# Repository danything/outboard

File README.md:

# outboard

An external board that powers a PCIe x1 TV tuner card from USB-C and connects it to a PC over the card's internal USB cable.
Status: pre-prototype. Nothing here has been built or tested on real hardware.
License: CERN-OHL-S-2.0.

## 何をする基板か

PLEX PX-MLT8PE のような PCIe x1 のチューナーカードは、PCIe からは電源 (3.3V と 12V) だけを取り、信号はカードの内部 USB ケーブルで出す。
outboard はその電源を USB-C (PD 9V) から作り、内部 USB を USB-C で PC へつなぐ。カードを PC の外に置ける。

- USB-C 2 口: J1 = PC へのデータ + 給電、J2 = 給電だけ
- カードの内部 USB の口 2 つ (機器 2 台) を、基板のハブ (CH334P) でまとめて J1 へ。カードとは JST PH 4 ピンのケーブル 2 本
- PCIe x1 のスロット J3 は基板の端をはさむ形 (straddle)。カードは基板と同じ平面に並ぶ (ケースを薄くするため)
- 回路と理由は [docs/design.md](docs/design.md)

## 状態

**rev D・試作前。実機では未検証。** 版の名前は rev D のままだが、KiCad の rev D からハブと PH のコネクタの分 (と外部のレビューでの直し) だけ違う。次の版は rev E。KiCad + Python のスクリプトから [tscircuit](https://tscircuit.com) (TypeScript) へ作り直した (段階 5 の製造用の出力と文書の仕上げが残り)。

| 段階 | 中身                                                                   | 状態                                            |
| ---- | ---------------------------------------------------------------------- | ----------------------------------------------- |
| 0    | リポジトリの土台と CI/CD                                               | 済み                                            |
| 1    | フットプリント (データシートとの突き合わせ)                            | 済み ([docs/footprints.md](docs/footprints.md)) |
| 2    | 回路 (rev D のネットリスト + 変更の表と同じつながり方になることを検査) | 済み (食い違い 0)                               |
| 3    | 基板の検査 (自前)                                                      | 済み ([docs/checks.md](docs/checks.md))         |
| 4    | 配置と配線                                                             | 済み ([docs/routing.md](docs/routing.md))       |
| 5    | 製造用の出力と文書の仕上げ                                             |                                                 |

**回路は入った**: 部品 121 個・ネット 64 本・未接続のパッド 48 個が、rev D (KiCad) のネットリストに意図した変更の表 (`tools/netlist.ts`) を当てたものと完全に同じつながり方になっている (CI が毎回比べる)。
**USB のハブを足した**: カードは内部 USB の口を 2 つ持つ (機器 2 台) ので、2×5 のヘッダ J4 をやめ、ハブ U8 (CH334P) で 2 つに分けて、カードの口と同じ系統の JST PH 4 ピンの表面実装のコネクタ J4・J6 へ出す (両端 PH のケーブル 25cm × 2 本、同じ向き 1 → 1 でつなぐ)。カードの VBUS は専用の U9 (VBUS1 から) と、短絡の保護の PTC F2 を通して出す。基板は 100 × 42mm のまま。**J4・J6 のピンの割り当て (1 VBUS・2 D−・3 D+・4 GND) は元のケーブルの線の色からの推定で、確かめ待ち** (`lib/card-usb.ts` の 1 か所で変えられる。[design.md](docs/design.md#内部-usb-のコネクタ))。
**配線は完了。発注前の最終レビュー待ち。** 部品は `lib/placement.ts` に置き (ブロックごとの配置と、ブロックをまたぐネットの受け渡しの点。配置だけの絵は [`placement.circuit-pcb.snap.svg`](__snapshots__/placement.circuit-pcb.snap.svg))、銅は `lib/routing/` にブロックごとの別ファイルで書いてある ([docs/routing.md](docs/routing.md))。基板は 100 × 42mm ([docs/mechanical.md](docs/mechanical.md#寸法))・2 層。部品番号はうらのシルク (`lib/refdes.tsx`)。
**検査は全部 0** (CI とリリースが毎回): 自前の検査は `bun checks/run.ts --strict` で指摘 0・飛ばし 0、回路の値 0、rev D とのネットリストの食い違い 0、KiCad の DRC は `lib_footprint_issues` (書き出しの名前の都合) のほか 0。ブロックをつなぐ所は検査 `handoffs`、うらの GND は `groundPlane` が見る。
D1・D2 の放熱は、このまま試作して温度を測る (持ち主の判断)。5V の入力のときは、ファームウェアが最初から 3.3V の負荷を制限する。rev E の候補: 理想ダイオード (TPS2121 など) への置き換え、カードの VBUS の U9 を過熱の保護つきの LDO に (どちらも試作の結果しだい)。製造で確かめることと、余裕の小さい所は [docs/manufacturing.md](docs/manufacturing.md#見積もりの画面で見る所)。

KiCad の版は main から消した。タグ [`kicad-rev-c`](../../tree/kicad-rev-c) (rev C。検査 0) と
ブランチ [`rev-d`](../../tree/rev-d) (rev D の途中。回路図とライブラリまで) に残っている。

## 主な仕様

| 項目     | 値                                                                                                                      |
| -------- | ----------------------------------------------------------------------------------------------------------------------- |
| 入力     | USB-C ×2、USB PD 9V (CH224A ×2)。2 口を SS54 で合流                                                                     |
| 出力     | 3.3V・3A (TPS62933)、12V・0.5A (MT3608B)。12V は AO3401A + PTC で入り切り、過電圧で遮断                                 |
| マイコン | CH32V003 (電源の順序・監視・LED)                                                                                        |
| 基板     | 2 層・厚み 1.6mm (J3 のため)。100 × 42mm                                                                                |
| ケース   | 光造形 (JLC3DP の 9600)。外形 約 145 × 151 × 21mm (カードの寸法は推定。[docs/mechanical.md](docs/mechanical.md#ケース)) |

## 見方

- ブラウザで見る (main の最新。基板・回路図・3D): <https://danything.github.io/outboard/>
- 絵は [`__snapshots__/`](__snapshots__/) にある (回路図・おもてとうら・おもて・うら・3D)。PR では絵の差分として変化が見える
- 3D の絵は部品を載せた姿 (形は [`lib/cad.ts`](lib/cad.ts) がデータシートの寸法から作る簡単なもの)。カードとブラケットは推定の寸法で、半透明・途中で切って描く (発注のデータには入らない)。
  斜め上・真上・横・USB-C の側の 4 枚 (`tools/render3d.ts`)。Pages にも同じ絵がある (`index/3d.png`・`index/3d-top.png`・`index/3d-side.png`・`index/3d-usb.png`)

| 回路図                                                    | 3D                                             |
| --------------------------------------------------------- | ---------------------------------------------- |
|  |  |

| 3D (USB-C とブラケットの側)                              | 3D (真上)                                               |
| -------------------------------------------------------- | ------------------------------------------------------- |
|  |  |

## 作り方

道具はコンテナだけ (ホストに Bun も Node も入れない)。CI と同じイメージの中で動かす。中身は [compose.yml](compose.yml)。

```sh
docker compose up dev               # 起動。http://localhost:3020 に基板・回路図・3D (保存すると描き直す)
docker compose run --rm check       # 検査。CI の build と同じ一式 (下の script を全部)
docker compose run --rm snapshots   # 絵の更新 (__snapshots__ を描き直す)
docker compose run --rm kicad-drc   # KiCad の DRC。check に続けて KiCad の DRC と判定 (CI の全部)
```

- Zed で書くとき: コードは Zed、動く画面は横のブラウザで <http://localhost:3020> (main の最新でよければ [Pages](https://danything.github.io/outboard/))。
  絵だけ見るなら `__snapshots__/`。変えたら `snapshots` で描き直して、差分ごとコミットする
- wslc には compose が無い (3.0)。同じ中身を `run` で動かす。起動は下の 1 行。ほかは `-p` と `-e` を外し、`sh -c` の中身を compose.yml の `command` に替える
  (KiCad の DRC は `check` のあと、`--user 0 -w /work/dist/index/kicad kicad/kicad:10.0` で `kicad-cli`、続けて Bun で判定)。Git Bash では前に `MSYS_NO_PATHCONV=1` を付ける

```sh
wslc run --rm -it -p 127.0.0.1:3020:3020 -e CHOKIDAR_USEPOLLING=true -v .:/work -v outboard_node_modules:/work/node_modules -w /work oven/bun:1.4.4 sh -c "bun install --frozen-lockfile && bunx tsci dev"
```

script を 1 つずつ動かすときは、中に入る (`docker compose run --rm check bash`)。

```sh
bun run build      # dist/ に circuit.json・絵・KiCad の基板・見るためのページ
bun run check      # 型検査 (bun check)・テスト (bun test)・自前の検査 (基板・回路の値・rev D とのネットリストの比べ)
bun run snapshot   # __snapshots__ の絵と同じか。変えたときは bun run snapshot --update
bun run fab        # dist/fab/ に製造用のファイル一式
bun run case       # dist/case/ にケース (皿・ふた・ハッチ) の STL と STEP、絵 (先に build)
bun run lint       # oxlint と bun fmt --check。直すときは bun run format
```

- 版は全部固定してある (tscircuit は 0.0.x が 1 日に何度も出る)。上げるのは Renovate
- ビルドは外の部品検索に問い合わせない (`--disable-parts-engine`)。設計を tscircuit.com に送らない
- `tsci dev` には切る指定が無く、部品の品番を外の部品検索に問い合わせることがある (tscircuit 0.0.3161 の `<board>` にも切る指定は無い)
- `typescript` は入れていない。型検査は `bun check`。`circuit-json` は circuit.json の型のために入れてある

| 場所                          | 中身                                                                                                                                                                                                                              |
| ----------------------------- | --------------------------------------------------------------------------------------------------------------------------------------------------------------------------------------------------------------------------------- |
| `index.circuit.tsx`           | 基板の全体                                                                                                                                                                                                                        |
| `lib/`                        | `blocks.tsx` (ブロックごとの回路)・`parts.tsx` (部品。ピンとネットを型で縛る)・`nets.ts` (ネットの一覧)・`footprints.ts` (ランド)・`placement.ts` (位置)・`routing/` (銅。ブロックごと)・`geometry.ts` (外形)・`revision.ts` (版) |
| `land-patterns.circuit.tsx`   | 全部のランドを並べた見本 (作る基板ではない)                                                                                                                                                                                       |
| `checks/`                     | circuit.json を読む自前の検査と、検査のテスト。`board.ts` (基板)・`design.ts` (分圧の値・定格など、回路の意図)                                                                                                                    |
| `case/`                       | ケース (replicad)。`card.ts` (カードの推定の寸法)・`layout.ts` (形)・`case.test.ts` (中身と重ならないか)                                                                                                                          |
| `tools/`                      | 製造用の出力・スナップショット・KiCad の DRC の判定・`netlist.ts` (rev D とのネットリストの比べ)                                                                                                                                  |
| `fixtures/rev-d-netlist.json` | rev D の KiCad のネットリスト (部品と、パッドごとのつながり)。比べる相手                                                                                                                                                          |

## CI/CD

| いつ                                                                | 何をする                                                                                                                                                               |
| ------------------------------------------------------------------- | ---------------------------------------------------------------------------------------------------------------------------------------------------------------------- |
| PR・main への push ([check.yml](.github/workflows/check.yml))       | lint → ビルド (tscircuit の検査を含む) → 型検査・テスト・自前の検査 (rev D とのネットリストの比べを含む) → スナップショット → 製造用の出力 → ケース → **KiCad の DRC** |
| main への push                                                      | 上に加えて、見るためのページを GitHub Pages に出す                                                                                                                     |
| タグ `rev-*` の push ([release.yml](.github/workflows/release.yml)) | 同じ手順で作った製造用のファイルを GitHub Release に添付                                                                                                               |

- **二重の検査**: tscircuit が書き出した KiCad の基板に、KiCad 10 の DRC (`--refill-zones`) をかける。
  つながっていない所・短絡・面を塗り直したあとの間隔を見る。自前の検査との役割の分け方は [docs/checks.md](docs/checks.md)。
  書き出しのせいで出る指摘は、理由を付けて [tools/kicad-drc.ts](tools/kicad-drc.ts) で除外する。決まり ([tools/outboard.kicad_dru](tools/outboard.kicad_dru)) の数字は `checks/rules.ts` と同じ
- **成果物** (Actions の Artifacts): `fab` (ガーバーの zip・BOM・配置表・回路図の PDF・絵・circuit.json・SHA256SUMS)、`case` (ケースの STL・STEP・絵)、`site` (ページ)、`kicad-drc` (DRC の報告)
- **必須のチェック** (ルールセット `default`): `build / build`・`build / kicad-drc`・`claude-review`。緑になるまで main にマージできない。CI のジョブを足したり名前を変えたりしたら、ルールセットも直す: `gh api repos/danything/outboard/rulesets --jq '.[]|select(.name=="default").id'` で id を引き、`gh api -X PUT repos/danything/outboard/rulesets/<id> --input <直した JSON>`
- **スナップショット**: 絵が 1 つでも変わると CI が落ちる。Renovate の PR は、絵が変わらないときだけ自分でマージされる
- **リリース**: `lib/revision.ts` の版 (基板のシルクと同じ) と同じ名前のタグを main のコミットに打って push する。
  **発注するデータは必ずリリースから取る**。同じ版は出し直せないので、基板を変えたら版を上げる

## 文書

| ファイル                                       | 中身                                                               |
| ---------------------------------------------- | ------------------------------------------------------------------ |
| [docs/design.md](docs/design.md)               | ブロック図、ブロックごとの回路、つなぎ方ごとの動き、電力の見積もり |
| [docs/parts.md](docs/parts.md)                 | 部品と選んだ理由、LCSC の品番                                      |
| [docs/footprints.md](docs/footprints.md)       | ランドとデータシートの突き合わせの表、部品データの出どころ         |
| [docs/mechanical.md](docs/mechanical.md)       | 形の選び方、寸法、ブラケット、ケース、実物で測る所                 |
| [docs/firmware.md](docs/firmware.md)           | ファームウェアの仕様、LED の点滅                                   |
| [docs/manufacturing.md](docs/manufacturing.md) | JLCPCB への出し方、見積もり、ケースの JLC3DP への出し方            |
| [docs/bringup.md](docs/bringup.md)             | 試作で最初に測ること、試験の一覧                                   |
| [docs/history.md](docs/history.md)             | rev A〜C のレビューで決めたこと (いまの設計の理由)                 |
| [docs/checks.md](docs/checks.md)               | 基板の検査の一覧、自前の検査と KiCad の DRC の役割の分け方         |
| [docs/routing.md](docs/routing.md)             | 配線の書き方 (ファイルの分け方、層、座標、部品、確かめ方)          |

## ライセンス

[CERN-OHL-S-2.0](LICENSE)

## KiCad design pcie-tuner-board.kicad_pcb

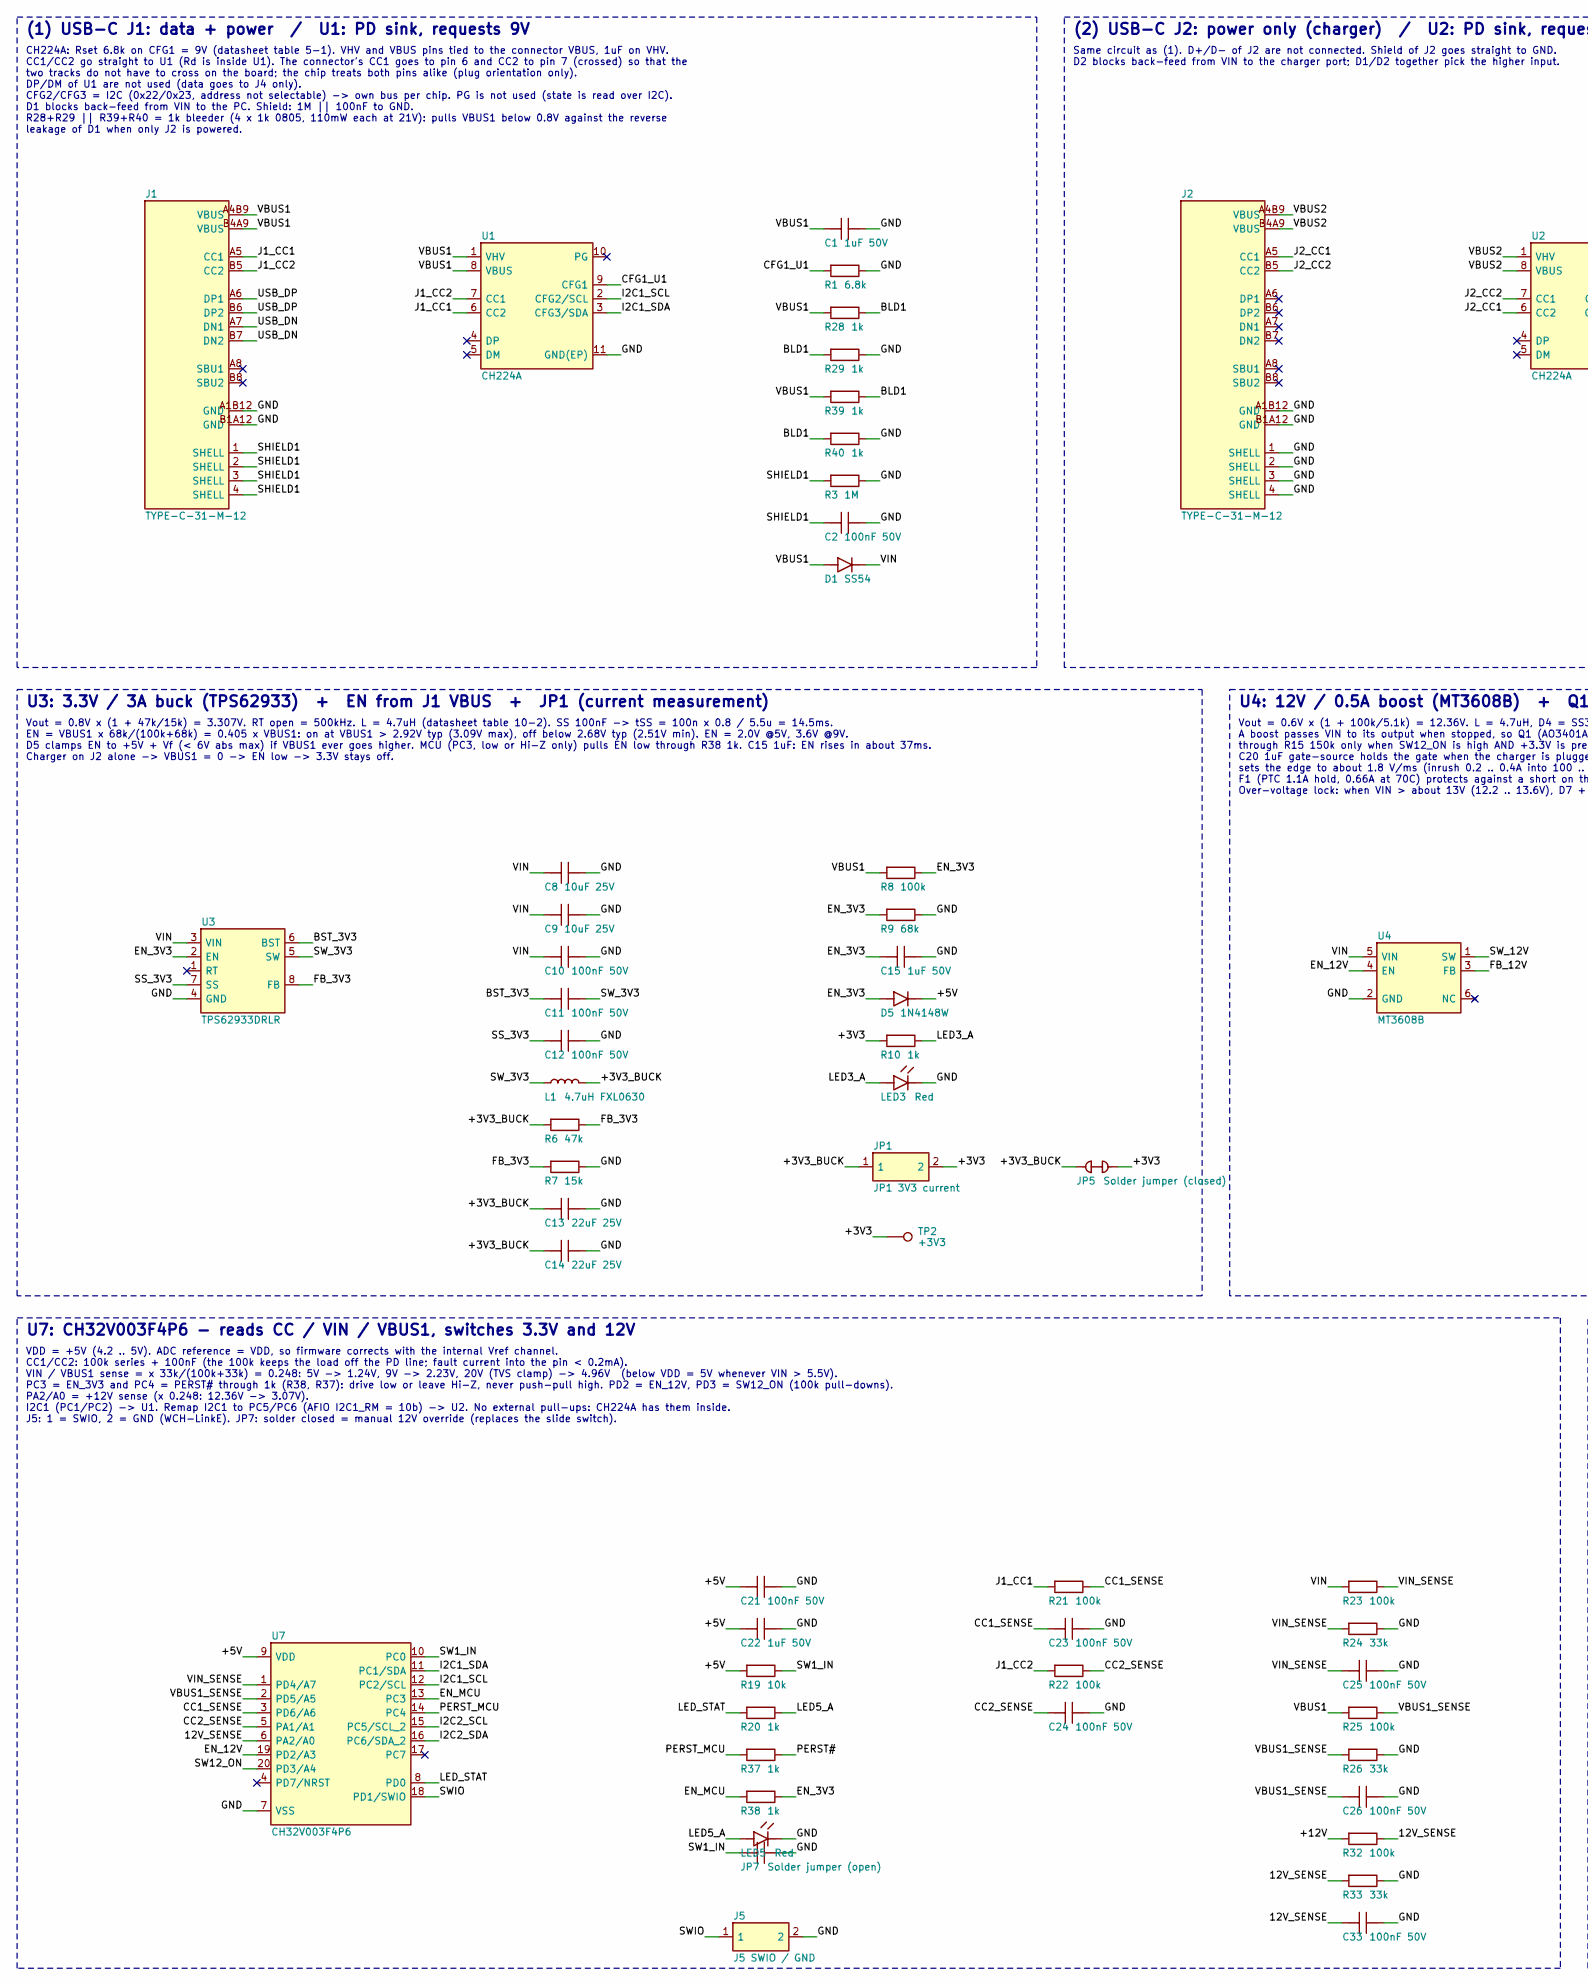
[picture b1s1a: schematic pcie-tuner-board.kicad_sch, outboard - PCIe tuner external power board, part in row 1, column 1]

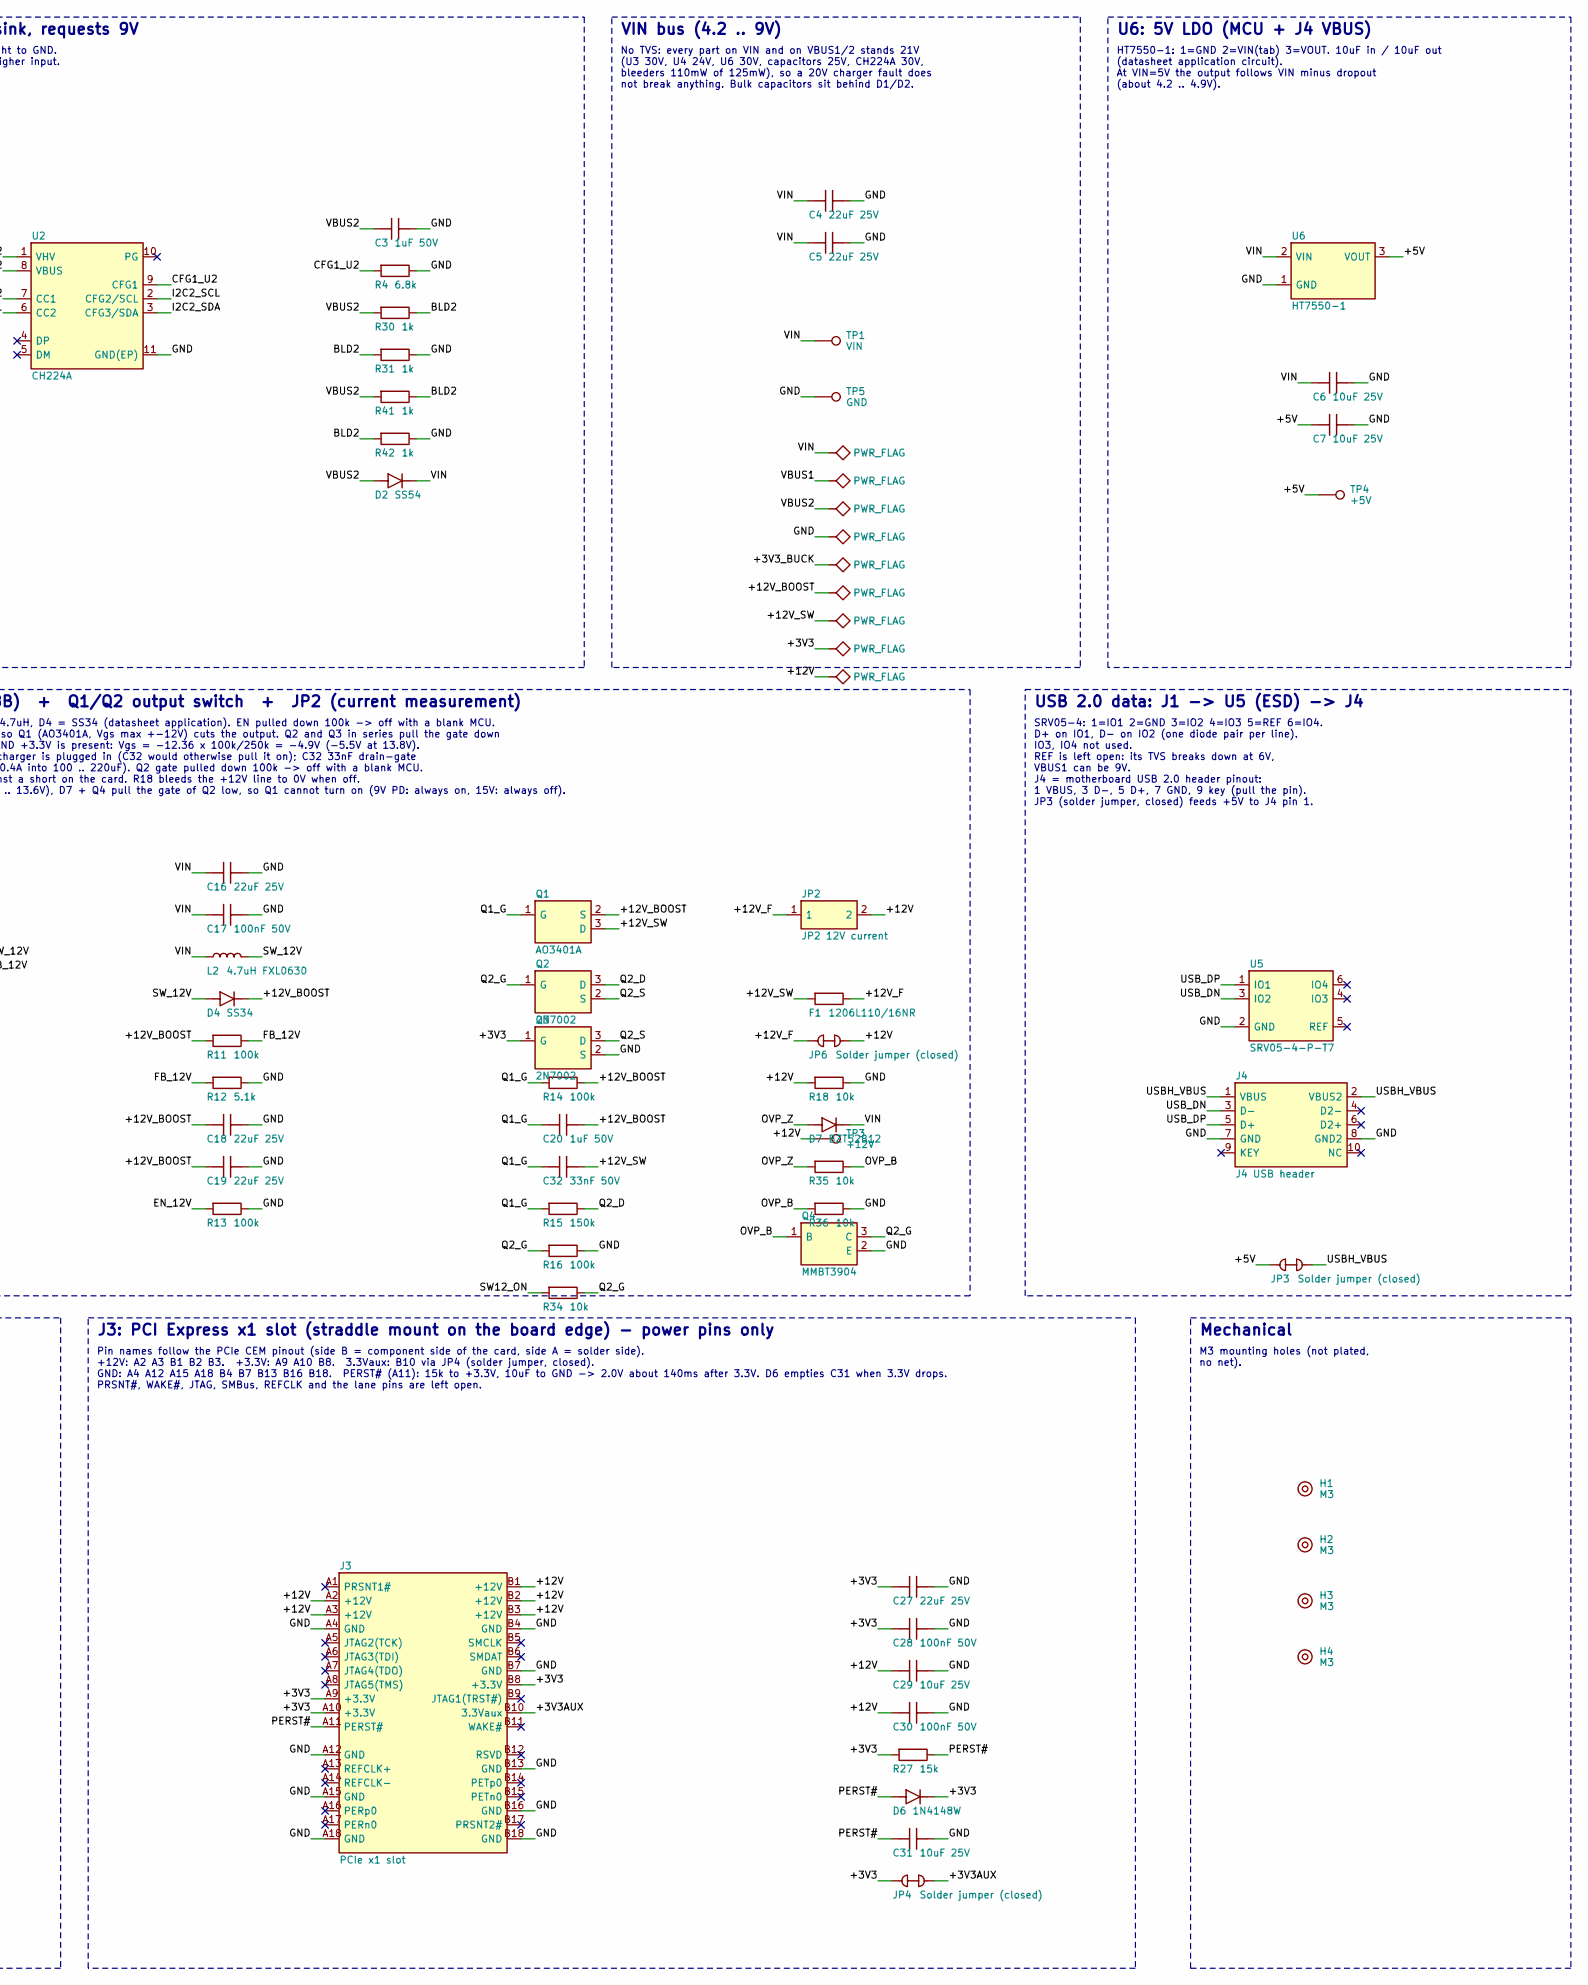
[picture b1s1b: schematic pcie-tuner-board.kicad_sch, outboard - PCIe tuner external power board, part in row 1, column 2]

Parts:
C1, C3, C15, C20, C22: 1uF 50V; C0603; MPN CL10A105KB8NNNC; LCSC C15849
C2, C10, C11, C12, C17, C21, C23, C24, C25, C26, C28, C30, C33: 100nF 50V; C0603; MPN CC0603KRX7R9BB104; LCSC C14663
C4, C5, C13, C14, C16, C18, C19, C27: 22uF 25V; C0805; MPN CL21A226MAQNNNE; LCSC C45783
C6, C7, C8, C9, C29, C31: 10uF 25V; C0805; MPN CL21A106KAYNNNE; LCSC C15850
C32: 33nF 50V; C0603; MPN CL10B333KB8NNNC; LCSC C21117
D1, D2: SS54; SMA_L4.4-W2.8-LS5.4-R-RD; MPN SS54; LCSC C22452
D4: SS34; SMA_L4.3-W2.6-LS5.2-RD; MPN SS34; LCSC C8678
D5, D6: 1N4148W; SOD-123F_L2.7-W1.6-LS3.8-RD; MPN 1N4148W; LCSC C81598
D7: BZT52B12; SOD-123_L2.7-W1.6-LS3.7-RD; MPN BZT52B12; LCSC C22395569
F1: 1206L110/16NR; F1206; MPN 1206L110/16NR; LCSC C7542961
H1, H2, H3, H4: M3; MountingHole_3.2mm_M3
J1, J2: TYPE-C-31-M-12; USB-C_SMD-TYPE-C-31-M-12_1; MPN TYPE-C-31-M-12; LCSC C165948
J3: PCIe x1 slot; CONN-SMD_36P-P1.00_X1613WS-36-9TV01; MPN X1613WS-36D-9TV01; LCSC C21263091
J4: J4 USB header; HDR-TH_10P-P2.54-H-M-R2-C5-S2.54; MPN PZ254R-12-10P; LCSC C492433
J5: J5 SWIO / GND; HDR-TH_2P-P2.54-V-M; MPN PZ254V-11-02P
JP1: JP1 3V3 current; HDR-TH_2P-P2.54-V-M; MPN PZ254V-11-02P
JP2: JP2 12V current; HDR-TH_2P-P2.54-V-M; MPN PZ254V-11-02P
JP3, JP4, JP5, JP6: Solder jumper (closed); SolderJumper-2_P1.3mm_Bridged_RoundedPad1.0x1.5mm
JP7: Solder jumper (open); SolderJumper-2_P1.3mm_Open_RoundedPad1.0x1.5mm
L1, L2: 4.7uH FXL0630; IND-SMD_L7.0-W6.6; MPN FXL0630-4R7-M; LCSC C167220
LED3, LED5: Red; LED-SMD_L1.6-W0.8-R-RD; MPN KT-0603R; LCSC C2286
Q1: AO3401A; SOT-23_L2.9-W1.3-P1.90-LS2.4-BR; MPN AO3401A; LCSC C15127
Q2, Q3: 2N7002; SOT-23-3_L2.9-W1.3-P1.90-LS2.4-BR; MPN 2N7002; LCSC C8545
Q4: MMBT3904; SOT-23-3_L2.9-W1.3-P1.90-LS2.4-BR; MPN MMBT3904; LCSC C20526
R1, R4: 6.8k; R0603; MPN 0603WAF6801T5E; LCSC C23212
R3: 1M; R0603; MPN 0603WAF1004T5E; LCSC C22935
R6: 47k; R0603; MPN 0603WAF4702T5E; LCSC C25819
R7, R27: 15k; R0603; MPN 0603WAF1502T5E; LCSC C22809
R8, R11, R13, R14, R16, R21, R22, R23, R25, R32: 100k; R0603; MPN 0603WAF1003T5E; LCSC C25803
R9: 68k; R0603; MPN 0603WAF6802T5E; LCSC C23231
R10, R20, R37, R38: 1k; R0603; MPN 0603WAF1001T5E; LCSC C21190
R12: 5.1k; R0603; MPN 0603WAF5101T5E; LCSC C23186
R15: 150k; R0603; MPN 0603WAF1503T5E; LCSC C22807
R18, R19, R34, R35, R36: 10k; R0603; MPN 0603WAF1002T5E; LCSC C25804
R24, R26, R33: 33k; R0603; MPN 0603WAF3302T5E; LCSC C4216
R28, R29, R30, R31, R39, R40, R41, R42: 1k; R0805; MPN 0805W8F1001T5E; LCSC C17513
TP1: VIN; TestPoint_Pad_D1.5mm
TP2: +3V3; TestPoint_Pad_D1.5mm
TP3: +12V; TestPoint_Pad_D1.5mm
TP4: +5V; TestPoint_Pad_D1.5mm
TP5: GND; TestPoint_Pad_D1.5mm
U1, U2: CH224A; ESSOP-10_L4.9-W3.9-P1.0-LS6.0-TL-EP; MPN CH224A; LCSC C42459160
U3: TPS62933DRLR; SOT-583-8_L2.1-W1.2-P0.50-LS1.6-BR; MPN TPS62933DRLR; LCSC C3200405
U4: MT3608B; SOT-23-6_L2.9-W1.6-P0.95-LS2.8-BR; MPN MT3608B; LCSC C19189893
U5: SRV05-4-P-T7; SOT-23-6_L2.9-W1.6-P0.95-LS2.8-BR; MPN SRV05-4-P-T7; LCSC C85364
U6: HT7550-1; SOT-89-3_L4.5-W2.5-P1.50-LS4.2-BR; MPN HT7550-1; LCSC C16106
U7: CH32V003F4P6; TSSOP-20_L6.5-W4.4-P0.65-LS6.4-BL; MPN CH32V003F4P6; LCSC C5187096

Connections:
/12V_SENSE: C33.1, R32.2, R33.1, U7.6 (PA2/A0)
/+3V3: C27.1, C28.1, D6.1 (K), J3.A9 (+3.3V), J3.A10 (+3.3V), J3.B8 (+3.3V), JP1.2, JP4.1, JP5.2, Q3.1 (G), R10.1, R27.1, TP2.1
/+3V3AUX: J3.B10 (3.3Vaux), JP4.2
/+3V3_BUCK: C13.1, C14.1, JP1.1, JP5.1, L1.2, R6.1
/+5V: C7.1, C21.1, C22.1, D5.1 (K), JP3.1, R19.1, TP4.1, U6.3 (VOUT), U7.9 (VDD)
/+12V: C29.1, C30.1, J3.A2 (+12V), J3.A3 (+12V), J3.B1 (+12V), J3.B2 (+12V), J3.B3 (+12V), JP2.2, JP6.2, R18.1, R32.1, TP3.1
/+12V_BOOST: C18.1, C19.1, C20.2, D4.1 (K), Q1.2 (S), R11.1, R14.2
/+12V_F: F1.2, JP2.1, JP6.1
/+12V_SW: C32.2, F1.1, Q1.3 (D)
/BLD1: R28.2, R29.1, R39.2, R40.1
/BLD2: R30.2, R31.1, R41.2, R42.1
/BST_3V3: C11.1, U3.6 (BST)
/CC1_SENSE: C23.1, R21.2, U7.3 (PD6/A6)
/CC2_SENSE: C24.1, R22.2, U7.5 (PA1/A1)
/CFG1_U1: R1.1, U1.9 (CFG1)
/CFG1_U2: R4.1, U2.9 (CFG1)
/EN_3V3: C15.1, D5.2 (A), R8.2, R9.1, R38.2, U3.2 (EN)
/EN_12V: R13.1, U4.4 (EN), U7.19 (PD2/A3)
/EN_MCU: R38.1, U7.13 (PC3)
/FB_3V3: R6.2, R7.1, U3.8 (FB)
/FB_12V: R11.2, R12.1, U4.3 (FB)
/GND: C1.2, C2.2, C3.2, C4.2, C5.2, C6.2, C7.2, C8.2, C9.2, C10.2, C12.2, C13.2, C14.2, C15.2, C16.2, C17.2, C18.2, C19.2, C21.2, C22.2, C23.2, C24.2, C25.2, C26.2, C27.2, C28.2, C29.2, C30.2, C31.2, C33.2, J1.A1B12 (GND), J1.B1A12 (GND), J2.1 (SHELL), J2.2 (SHELL), J2.3 (SHELL), J2.4 (SHELL), J2.A1B12 (GND), J2.B1A12 (GND), J3.A4 (GND), J3.A12 (GND), J3.A15 (GND), J3.A18 (GND), J3.B4 (GND), J3.B7 (GND), J3.B13 (GND), J3.B16 (GND), J3.B18 (GND), J4.7 (GND), J4.8 (GND2), J5.2, JP7.2, LED3.2 (K), LED5.2 (K), Q3.2 (S), Q4.2 (E), R1.2, R3.2, R4.2, R7.2, R9.2, R12.2, R13.2, R16.2, R18.2, R24.2, R26.2, R29.2, R31.2, R33.2, R36.2, R40.2, R42.2, TP5.1, U1.11 (GND(EP)), U2.11 (GND(EP)), U3.4 (GND), U4.2 (GND), U5.2 (GND), U6.1 (GND), U7.7 (VSS)
/I2C1_SCL: U1.2 (CFG2/SCL), U7.12 (PC2/SCL)
/I2C1_SDA: U1.3 (CFG3/SDA), U7.11 (PC1/SDA)
/I2C2_SCL: U2.2 (CFG2/SCL), U7.15 (PC5/SCL_2)
/I2C2_SDA: U2.3 (CFG3/SDA), U7.16 (PC6/SDA_2)
/J1_CC1: J1.A5 (CC1), R21.1, U1.6 (CC2)
/J1_CC2: J1.B5 (CC2), R22.1, U1.7 (CC1)
/J2_CC1: J2.A5 (CC1), U2.6 (CC2)
/J2_CC2: J2.B5 (CC2), U2.7 (CC1)
/LED3_A: LED3.1 (A), R10.2
/LED5_A: LED5.1 (A), R20.2
/LED_STAT: R20.1, U7.8 (PD0)
/OVP_B: Q4.1 (B), R35.2, R36.1
/OVP_Z: D7.2 (A), R35.1
/PERST#: C31.1, D6.2 (A), J3.A11 (PERST#), R27.2, R37.2
/PERST_MCU: R37.1, U7.14 (PC4)
/Q1_G: C20.1, C32.1, Q1.1 (G), R14.1, R15.1
/Q2_D: Q2.3 (D), R15.2
/Q2_G: Q2.1 (G), Q4.3 (C), R16.1, R34.2
/Q2_S: Q2.2 (S), Q3.3 (D)
/SHIELD1: C2.1, J1.1 (SHELL), J1.2 (SHELL), J1.3 (SHELL), J1.4 (SHELL), R3.1
/SS_3V3: C12.1, U3.7 (SS)
/SW1_IN: JP7.1, R19.2, U7.10 (PC0)
/SW12_ON: R34.1, U7.20 (PD3/A4)
/SWIO: J5.1, U7.18 (PD1/SWIO)
/SW_3V3: C11.2, L1.1, U3.5 (SW)
/SW_12V: D4.2 (A), L2.2, U4.1 (SW)
/USBH_VBUS: J4.1 (VBUS), J4.2 (VBUS2), JP3.2
/USB_DN: J1.A7 (DN1), J1.B7 (DN2), J4.3 (D-), U5.3 (IO2)
/USB_DP: J1.A6 (DP1), J1.B6 (DP2), J4.5 (D+), U5.1 (IO1)
/VBUS1: C1.1, D1.1 (A), J1.A4B9 (VBUS), J1.B4A9 (VBUS), R8.1, R25.1, R28.1, R39.1, U1.1 (VHV), U1.8 (VBUS)
/VBUS1_SENSE: C26.1, R25.2, R26.1, U7.2 (PD5/A5)
/VBUS2: C3.1, D2.1 (A), J2.A4B9 (VBUS), J2.B4A9 (VBUS), R30.1, R41.1, U2.1 (VHV), U2.8 (VBUS)
/VIN: C4.1, C5.1, C6.1, C8.1, C9.1, C10.1, C16.1, C17.1, D1.2 (K), D2.2 (K), D7.1 (K), L2.1, R23.1, TP1.1, U3.3 (VIN), U4.5 (VIN), U6.2 (VIN)
/VIN_SENSE: C25.1, R23.2, R24.1, U7.1 (PD4/A7)

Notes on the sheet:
Vout = 0.6V x (1 + 100k/5.1k) = 12.36V. L = 4.7uH, D4 = SS34 (datasheet application). EN pulled down 100k -> off with a blank MCU. A boost passes VIN to its output when stopped, so Q1 (AO3401A, Vgs max +-12V) cuts the output. Q2 and Q3 in series pull the gate down through R15 150k only when SW12_ON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
No TVS: every part on VIN and on VBUS1/2 stands 21V (U3 30V, U4 24V, U6 30V, capacitors 25V, CH224A 30V, bleeders 110mW of 125mW), so a 20V charger fault does not break anything. Bulk capacitors sit behind D1/D2.
Vout = 0.8V x (1 + 47k/15k) = 3.307V. RT open = 500kHz. L = 4.7uH (datasheet table 10-2). SS 100nF -> tSS = 100n x 0.8 / 5.5u = 14.5ms. EN = VBUS1 x 68k/(100k+68k) = 0.405 x VBUS1: on at VBUS1 > 2.92V typ (3.09V max), off below 2.68V typ (2.51V min). EN = 2.0V @5V, 3.6V @9V. D5 clamps EN to +5V + V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
Mechanical
Same circuit as (1). D+/D- of J2 are not connected. Shield of J2 goes straight to GND. D2 blocks back-feed from VIN to the charger port; D1/D2 together pick the higher input.
CH224A: Rset 6.8k on CFG1 = 9V (datasheet table 5-1). VHV and VBUS pins tied to the connector VBUS, 1uF on VHV. CC1/CC2 go straight to U1 (Rd is inside U1). The connector's CC1 goes to pin 6 and CC2 to pin 7 (crossed) so that the two tracks do not have to cross on the board; the chip treats both pi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
USB 2.0 data: J1 -> U5 (ESD) -> J4
Pin names follow the PCIe CEM pinout (side B = component side of the card, side A = solder side). +12V: A2 A3 B1 B2 B3. +3.3V: A9 A10 B8. 3.3Vaux: B10 via JP4 (solder jumper, closed). GND: A4 A12 A15 A18 B4 B7 B13 B16 B18. PERST# (A11): 15k to +3.3V, 10uF to GND -> 2.0V about 140ms after 3.3V. D6 e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
U4: 12V / 0.5A boost (MT3608B) + Q1/Q2 output switch + JP2 (current measurement)
SRV05-4: 1=IO1 2=GND 3=IO2 4=IO3 5=REF 6=IO4. D+ on IO1, D- on IO2 (one diode pair per line). IO3, IO4 not used. REF is left open: its TVS breaks down at 6V, VBUS1 can be 9V. J4 = motherboard USB 2.0 header pinout: 1 VBUS, 3 D-, 5 D+, 7 GND, 9 key (pull the pin). JP3 (solder jumper, closed) feeds +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
VDD = +5V (4.2 .. 5V). ADC reference = VDD, so firmware corrects with the internal Vref channel. CC1/CC2: 100k series + 100nF (the 100k keeps the load off the PD line; fault current into the pin < 0.2mA). VIN / VBUS1 sense = x 33k/(100k+33k) = 0.248: 5V -> 1.24V, 9V -> 2.23V, 20V (TVS clamp) -> 4.9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
HT7550-1: 1=GND 2=VIN(tab) 3=VOUT. 10uF in / 10uF out (datasheet application circuit). At VIN=5V the output follows VIN minus dropout (about 4.2 .. 4.9V).
VIN bus (4.2 .. 9V)
U3: 3.3V / 3A buck (TPS62933) + EN from J1 VBUS + JP1 (current measurement)
(1) USB-C J1: data + power / U1: PD sink, requests 9V
U6: 5V LDO (MCU + J4 VBUS)
U7: CH32V003F4P6 - reads CC / VIN / VBUS1, switches 3.3V and 12V
J3: PCI Express x1 slot (straddle mount on the board edge) - power pins only
(2) USB-C J2: power only (charger) / U2: PD sink, requests 9V
M3 mounting holes (not plated, no net).

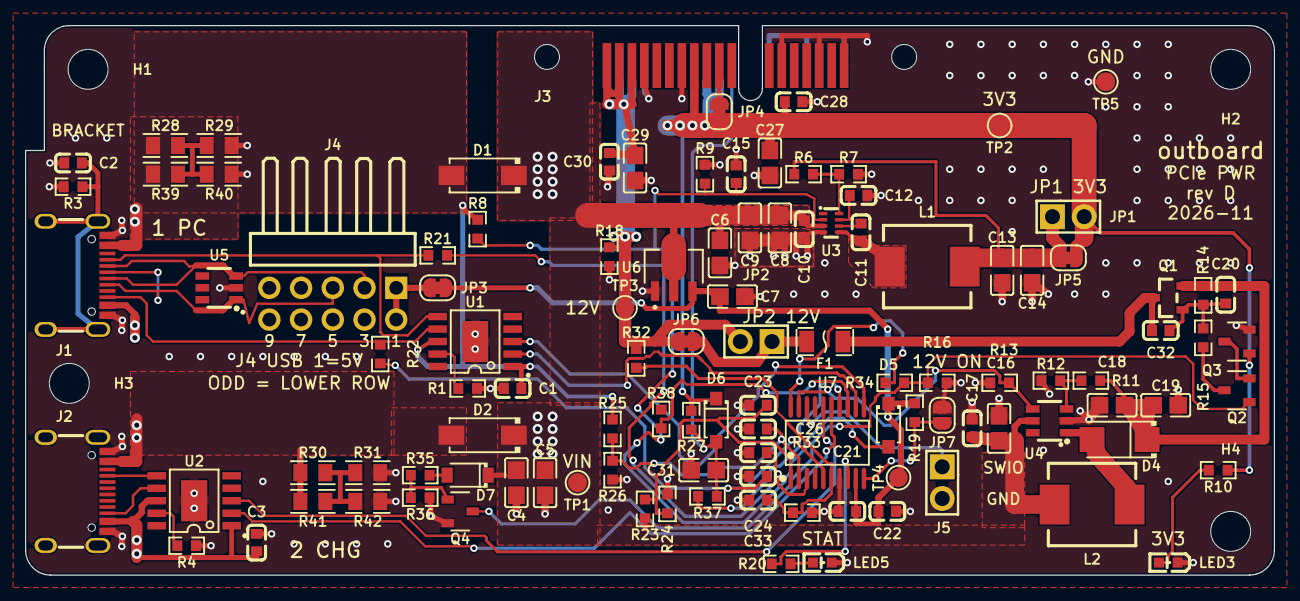
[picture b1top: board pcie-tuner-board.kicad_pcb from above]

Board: 2 copper layers, 100.0 x 44.0 mm, 115 parts (0 on the bottom side), 56 nets.

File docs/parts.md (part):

# 部品

outboard (rev D) の部品と選んだ理由、JLCPCB の区分 (Basic / Preferred / Extended)、LCSC の品番を書く。
区分と在庫は JLCPCB の部品検索を 2026-11-11〜12 に読んだ値で、発注の日に見積もりの画面で確かめ直す。

## 部品の一覧

部品は全部で 115 個。おもて面だけに載せる。回路でのつなぎ方は [design.md](design.md#ブロックごとの回路)。

| 部品                       | 型番                             | LCSC      | 区分      | 役目・選んだ理由                                                                                                                                         |
| -------------------------- | -------------------------------- | --------- | --------- | -------------------------------------------------------------------------------------------------------------------------------------------------------- |
| J1・J2                     | TYPE-C-31-M-12 (Korean Hroparts) | C165948   | Extended  | USB-C 16 ピン                                                                                                                                            |
| J3                         | X1613WS-36D-9TV01 (XKB)          | C21263091 | Extended  | PCIe x1 スロット。基板の端をまたぐ形 (straddle)、1.57mm の基板用。選んだ理由は [mechanical.md](mechanical.md#形の選び方)。在庫 604 (2026-11-12) と少ない |
| J4                         | PZ254R-12-10P (XFCN)             | C492433   | Extended  | 2×5 ピンヘッダ 2.54mm、横向き。まっすぐの形は厚みに収まらない ([ケースの内寸](mechanical.md#ケースの内寸))                                               |
| J5・JP1・JP2               | PZ254V-11-02P (XFCN)             | (C492401) | 載せない  | 1×2 ピンヘッダ。穴だけ作る                                                                                                                               |
| U1・U2                     | CH224A (WCH)                     | C42459160 | Extended  | USB PD のシンク。9V を要求する                                                                                                                           |
| U3                         | TPS62933DRLR (TI)                | C3200405  | Extended  | 降圧 3.8〜30V・3A。3.3V を作る                                                                                                                           |
| U4                         | MT3608B (Aerosemi)               | C19189893 | Extended  | 昇圧。12V を作る                                                                                                                                         |
| U5                         | SRV05-4-P-T7 (ProTek)            | C85364    | Preferred | USB のデータ線の ESD 保護                                                                                                                                |
| U6                         | HT7550-1 (Holtek)                | C16106    | Preferred | LDO 5V・100mA、入力 30V。マイコンと J4 の VBUS 用                                                                                                        |
| U7                         | CH32V003F4P6 (WCH)               | C5187096  | Extended  | マイコン、TSSOP20                                                                                                                                        |
| Q1                         | AO3401A (AOS)                    | C15127    | Basic     | P-MOSFET −30V、Vgs ±12V、Rds は −4.5V で最大 60mΩ。12V の出力スイッチ。AO3407A (Extended) の代わり                                                       |
| Q2・Q3                     | 2N7002 (Changjing)               | C8545     | Basic     | N-MOSFET 60V。Q1 のゲートを引く                                                                                                                          |
| Q4                         | MMBT3904 (CJ)                    | C20526    | Basic     | NPN。過電圧の遮断                                                                                                                                        |
| D1・D2                     | SS54 (MDD)                       | C22452    | Basic     | ショットキー 40V・5A。入力をまとめる。[SS54 と SSL54](#ss54-と-ssl54)                                                                                    |
| D4                         | SS34 (MDD)                       | C8678     | Basic     | ショットキー 40V・3A。昇圧の整流                                                                                                                         |
| D5・D6                     | 1N4148W                          | C81598    | Basic     | EN の電圧を抑える (D5)、PERST# のコンデンサを空にする (D6)                                                                                               |
| D7                         | BZT52B12                         | C22395569 | Preferred | ツェナー 12V ±2%、SOD-123。過電圧の遮断。Basic にツェナーは無い                                                                                          |
| L1・L2                     | FXL0630-4R7-M (cjiang)           | C167220   | Extended  | 4.7µH・6A                                                                                                                                                |
| F1                         | 1206L110/16NR (LUTE)             | C7542961  | Extended  | 自動復帰ヒューズ (PTC)、1206。[F1](#f1)                                                                                                                  |
| LED3・LED5                 | KT-0603R                         | C2286     | Basic     | 赤の 0603。横向きに光る LED は Basic・Preferred に無いので、ふつうの 0603 を辺のそばに置く                                                               |
| TP1〜TP5、H1〜H4、JP3〜JP7 | —                                | —         | 載せない  | テストポイント、取り付け穴、はんだジャンパー (銅だけ)                                                                                                    |

抵抗 (どれも Basic。0603・1%。ブリーダだけ 0805):

| 値               | LCSC   | 主な使い所                                  |
| ---------------- | ------ | ------------------------------------------- |
| 1kΩ              | C21190 | R37・R38 (マイコンと PERST#・EN の間の直列) |
| 1kΩ 0805 (125mW) | C17513 | R28〜R31・R39〜R42 (ブリーダ)               |
| 5.1kΩ            | C23186 | R12 (12V の分圧)                            |
| 6.8kΩ            | C23212 | R1・R4 (CH224A の CFG1)                     |
| 10kΩ             | C25804 | R34・R35・R36 など                          |
| 15kΩ             | C22809 | R7 (3.3V の分圧)、R27 (PERST#)              |
| 33kΩ             | C4216  | ADC の分圧の下                              |
| 47kΩ             | C25819 | R6 (3.3V の分圧)                            |
| 68kΩ             | C23231 | R9 (EN の分圧)                              |
| 100kΩ            | C25803 | R8・R11・R13・R14・R21・R22 など            |
| 150kΩ            | C22807 | R15 (Q1 のゲート)                           |
| 1MΩ              | C22935 | R3 など (USB-C の殻と GND の間)             |

コンデンサ (どれも Basic):

| 値             | LCSC   | 主な使い所                                |
| -------------- | ------ | ----------------------------------------- |
| 33nF 50V 0603  | C21117 | C32 (Q1 のドレイン-ゲート)                |
| 100nF 50V 0603 | C14663 | バイパス、C2 (USB-C の殻)                 |
| 1µF 50V 0603   | C15849 | C1・C3 (VHV)、C15 (EN)、C20 (Q1 のゲート) |
| 10µF 25V 0805  | C15850 | 電源の入力・出力、C31 (PERST#)            |
| 22µF 25V 0805  | C45783 | 3.3V の出力 (3 個) など                   |

VIN・VBUS・12V の線のコンデンサは、どれも耐圧 25V か 50V。

## 区分のまとめ

- **Extended は 9 種類**: USB-C、PCIe スロット、CH224A、TPS62933、MT3608B、CH32V003、4.7µH、PTC、2×5 ヘッダ
- **Preferred は 3 種類**: HT7550-1、BZT52B12、SRV05-4
- 残りは Basic

費用への効き方は [見積もり](manufacturing.md#見積もり)。

## Extended のまま残した理由

Basic (351 件) と Preferred (1,235 件) の全件から代わりを探した結果。

| 部品                             | Basic・Preferred を探した結果                                                                                                                                                                                                          |
| -------------------------------- | -------------------------------------------------------------------------------------------------------------------------------------------------------------------------------------------------------------------------------------- |
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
